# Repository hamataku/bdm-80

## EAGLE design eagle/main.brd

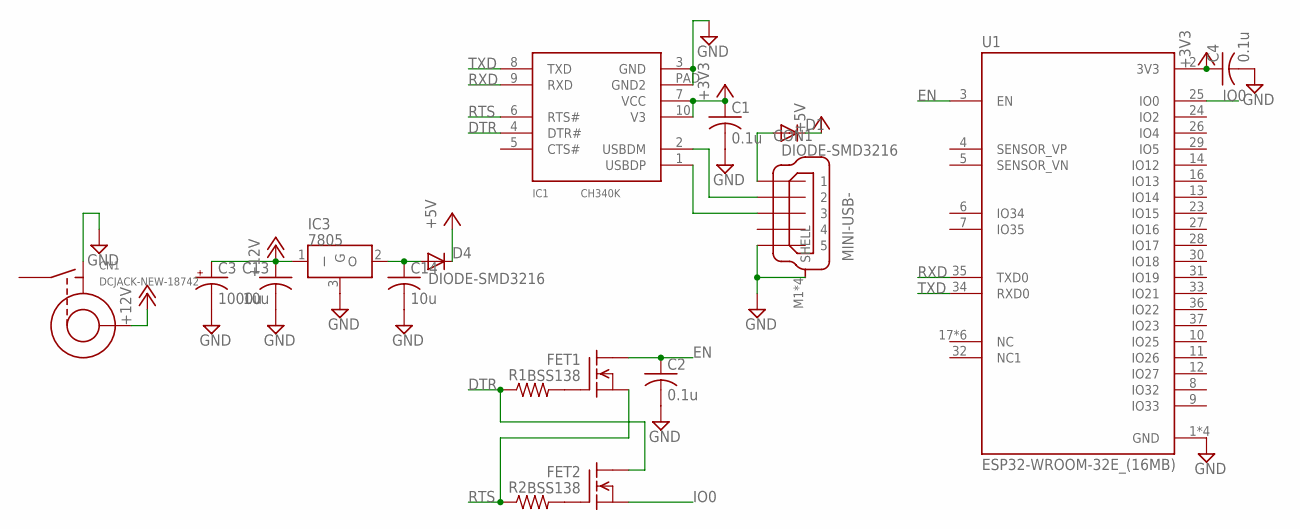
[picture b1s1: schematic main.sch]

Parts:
C1, C2, C4: 0.1u; 2012-C
C3: 1000u; E2,5-8
C13, C14: 10u; 3216
CN1: DCJACK-NEW-18742; 18742
CON1: MINI-USB-; UX60A-MB-5ST
D1, D4: DIODE-SMD3216; D3216
FET1, FET2: BSS138; SOT23
IC1: CH340K; HSSOP10
IC3: 7805; P-HSIP3_2.30A
R1, R2: R-2012; 2012-R
U1: ESP32-WROOM-32E_(16MB); XCVR_ESP32-WROOM-32E_(16MB)

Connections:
+3V3: C1.1, C4.1, IC1.7 (VCC), IC1.10 (V3), U1.2 (3V3)
+5V: D1.K (C), D4.K (C)
+12V: C3.+, C13.1, CN1.P$1 (CENTER), IC3.1 (I)
DTR: FET2.3 (D), IC1.4 (DTR#), R1.1
EN: C2.1, FET1.3 (D), U1.3 (EN)
GND: C1.2, C2.2, C3.-, C4.2, C13.2, C14.2, CN1.P$2 (TIP), CON1.5, CON1.M1 (SHELL), CON1.M2 (SHELL), CON1.M3 (SHELL), CON1.M4 (SHELL), IC1.3 (GND), IC1.PAD (GND2), IC3.3 (G), U1.1 (GND), U1.15 (GND), U1.38 (GND), U1.P$1 (GND)
IO0: FET2.2 (S), U1.25 (IO0)
unnamed: CON1.3, IC1.1 (USBDP)
unnamed: CON1.2, IC1.2 (USBDM)
unnamed: FET1.1 (G), R1.2
unnamed: FET2.1 (G), R2.2
unnamed: CON1.1, D1.A
O: C14.1, D4.A, IC3.2 (O)
RTS: FET1.2 (S), IC1.6 (RTS#), R2.1
RXD: IC1.9 (RXD), U1.35 (TXD0)
TXD: IC1.8 (TXD), U1.34 (RXD0)

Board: 2 copper layers, 17 parts (0 on the bottom side), 16 nets, no tracks yet.

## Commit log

2022-12-26 init
2022-12-26 rom修正
2022-12-27 touchgfx
2022-12-27 cmake
2022-12-28 touchgfxとtm1630が動作
2023-01-01 uart動く
2023-01-01 inputデバチェ
2023-01-06 急に動かない
2023-01-06 タイマ割り込みを高速化
2023-01-06 touchgfxダメです！
2023-01-08 ほぼ完成
2023-01-08 freqの保存
2023-01-10 とりあえず完成とする
2023-01-16 SIOとPIO動いた
2023-01-16 tm1630をrom側に移動
2023-01-19 basic動く
2023-01-19 BASICとPIOexの合体
2023-01-25 USB MSC ファイル認識できない
